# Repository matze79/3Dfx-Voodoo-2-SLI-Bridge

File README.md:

3Dfx Voodoo 2 SLI Bridge's

Non-3Dfx -> uses Custom Logo

3Dfx -> later 3Dfx Logo

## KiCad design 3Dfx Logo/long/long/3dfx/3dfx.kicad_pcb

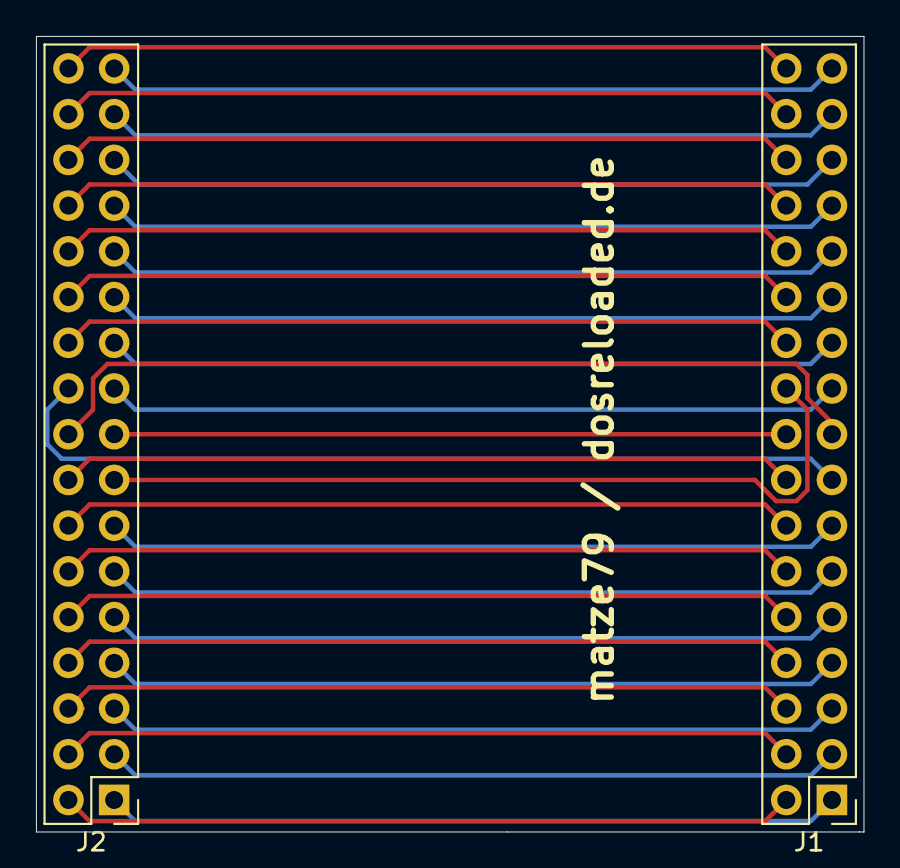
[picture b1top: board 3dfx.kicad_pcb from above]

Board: 2 copper layers, 46.0 x 44.2 mm, 3 parts (1 on the bottom side), 34 nets.

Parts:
J1, J2: Conn_02x17_Odd_Even; PinHeader_2x17_P2.54mm_Vertical
e: LOGO; 3dfx_2

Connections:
/D1: J1.2, J2.2
/D2: J1.1, J2.1
/D3: J1.4, J2.4
/D4: J1.3, J2.3
/D5: J1.6, J2.6
/D6: J1.5, J2.5
/D7: J1.8, J2.8
/D8: J1.7, J2.7
/D9: J1.10, J2.10
/D10: J1.9, J2.9
/D11: J1.12, J2.12
/D12: J1.11, J2.11
/D13: J1.14, J2.14
/D14: J1.13, J2.13
/D15: J1.16, J2.16
/D16: J1.20, J2.15
/D17: J1.17, J2.18
/D18: J1.18, J2.17
/D19: J1.15, J2.20
/D20: J1.19, J2.19
/D21: J1.22, J2.22
/D22: J1.21, J2.21
/D23: J1.24, J2.24
/D24: J1.23, J2.23
/D25: J1.26, J2.26
/D26: J1.25, J2.25
/D27: J1.28, J2.28
/D28: J1.27, J2.27
/D29: J1.30, J2.30
/D30: J1.29, J2.29
/D31: J1.32, J2.32
/D32: J1.31, J2.31
/D33: J1.34, J2.34
/D34: J1.33, J2.33

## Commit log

2025-11-23 3DFX Voodoo 2 SLI Bridge
    3Dfx SLI Bridge
2025-11-29 Update README to include custom logo note
    Add a note about the custom logo for Non-3Dfx.
